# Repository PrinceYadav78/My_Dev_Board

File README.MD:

##Note i dont want funding of 16$ as this includes a part of a different project

# RP2040 Breadboard-Friendly Devboard

A compact RP2040 devboard designed for rapid prototyping and breadboard use. This board allows testing GPIOs, sensors, and ideas without soldering every change.

## What is this?
This project is a small PCB with an RP2040 microcontroller, USB-C power input, and breadboard-compatible headers. It is designed to allow quick circuit testing, firmware development, and learning without requiring a polished final product.

## Why I made it
I wanted a board that could power over USB and plug directly into a breadboard for rapid experimentation. By designing this board, I learned how to plan pinout, power, and I/O for a microcontroller, while also learning schematic design and PCB layout in KiCad.

## How it works
Power enters via USB-C and goes through basic regulation and decoupling capacitors for stability. The RP2040 handles I/O and communicates with peripherals like an IMU (ICM-20602). LEDs indicate power, BootSel, and GPIO activity. Breadboard headers allow plugging in sensors or modules quickly, and proper routing ensures signal integrity and safe operation.

### Key features
- USB-C powered RP2040 board  
- Breadboard-compatible header layout  
- LEDs for power, BootSel, and GPIO  
- Integrated IMU (ICM-20602) with required decoupling caps  
- Crystal oscillator for accurate timing  
- Boot configuration with button and pull-ups  

## What I learned
- Schematic clean ≠ correct: always check net names and pin mapping  
- QSPI pins on RP2040 must go to dedicated flash pins for booting  
- Routing power and USB signals is tricky; differential pairs and trace lengths matter  
- Component placement affects ease of routing and board functionality  
- Breadboard compatibility must be considered from the start  

##Images of pcb, sch, cost, bom, etc

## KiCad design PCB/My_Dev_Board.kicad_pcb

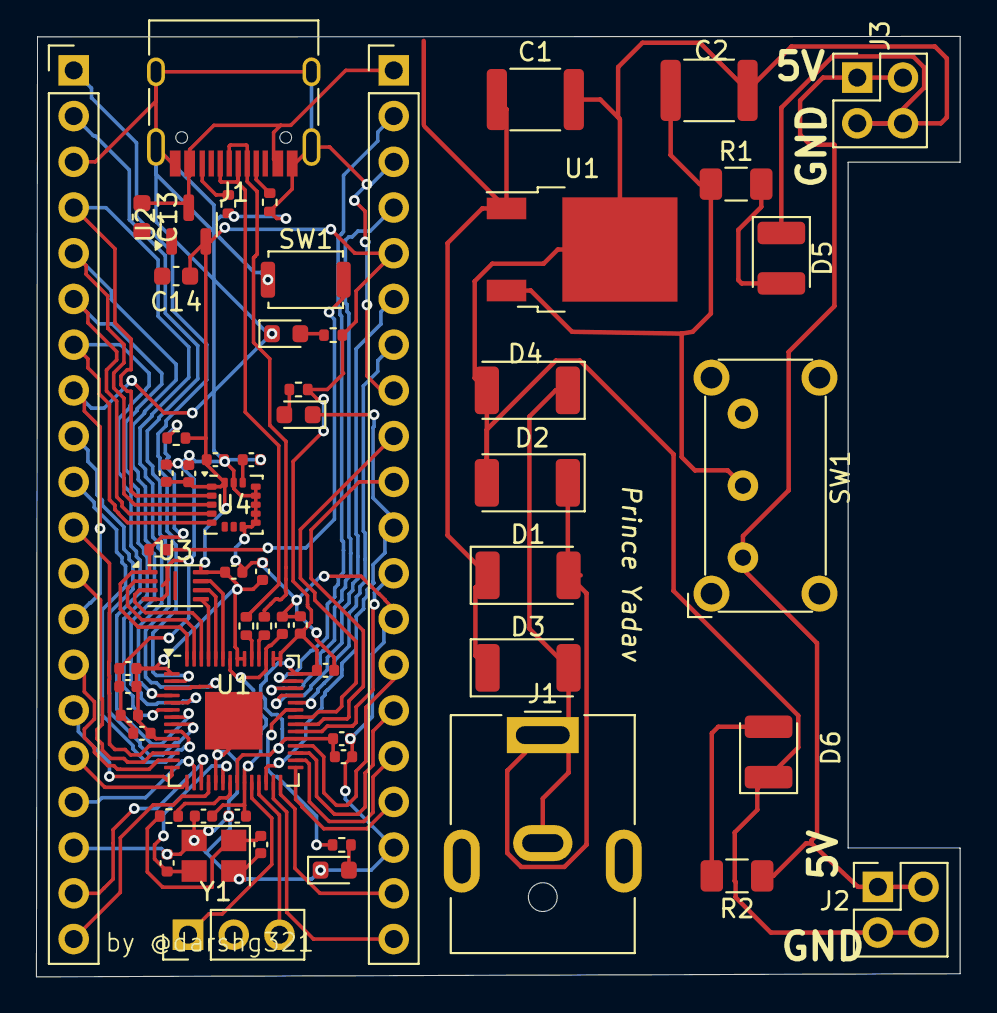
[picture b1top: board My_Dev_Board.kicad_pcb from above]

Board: 2 copper layers, 51.3 x 52.2 mm, 59 parts (0 on the bottom side), 65 nets.

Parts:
C1, C2#2, C3, C4, C5, C6, C7, C8, C10, C11, C17, C18, C20: 0.1uF; C_0402_1005Metric
C1#2: 47uF; C_1812_4532Metric
C2: 470uF; C_1812_4532Metric
C9, C12: 1uF; C_0402_1005Metric
C13, C14: 10uF; C_0603_1608Metric
C15, C16: 33pF; C_0402_1005Metric
C19: 10nF; C_0402_1005Metric
C21: 2.2uF; C_0402_1005Metric
D1, D2#2, D3: LED; LED_0603_1608Metric
D1#2, D2, D3#2, D4: 1N4007; D_2010_5025Metric
D5, D6: LED; LED_1210_3225Metric
J1: Barrel_Jack_Switch; BarrelJack_CUI_PJ-063AH_Horizontal
J1#2: USB_C_Receptacle_USB2.0_14P; USB_C_Receptacle_HRO_TYPE-C-31-M-12
J2, J3#2: Conn_01x20; PinHeader_1x20_P2.54mm_Vertical
J2#2, J3: Conn_02x02_Counter_Clockwise; PinHeader_2x02_P2.54mm_Vertical
J4: Conn_01x03; PinHeader_1x03_P2.54mm_Vertical
R1, R2#2: 560; R_1206_3216Metric
R1#2, R2: 5.1K; R_0402_1005Metric
R3, R4: 27; R_0402_1005Metric
R5, R7: 1K; R_0402_1005Metric
R6: 10K; R_0402_1005Metric
R8, R9, R10: 680; R_0402_1005Metric
SW1: SW_Push; SW_Push_SPST_NO_Alps_SKRK
SW1#2: SW_DPDT_x2; SW_E-Switch_EG1224_SPDT_Angled
U1: RP2040; QFN-56-1EP_7x7mm_P0.4mm_EP3.2x3.2mm
U1#2: LM7805_TO220; TO-252-2
U2: MCP1700x-330xxTT; SOT-23
U3: W25Q128JVS; Winbond_USON-8-1EP_3x2mm_P0.5mm_EP0.2x1.6mm
U4: ICM-20602; LGA-16_3x3mm_P0.5mm_LayoutBorder3x5y
Y1: 12MHz; Crystal_SMD_3225-4Pin_3.2x2.5mm

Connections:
+1V1: C10.1, C11.1, C12.1, U1.23 (DVDD), U1.45 (VREG_VOUT), U1.50 (DVDD)
+3V3: C1.1, C2#2.1, C3.1, C4.1, C5.1, C6.1, C7.1, C8.1, C9.1, C14.1, C17.1, C19.1, C20.2, C21.2, J3#2.5, R6.1, R8.1, R9.1, U1.1 (IOVDD), U1.10 (IOVDD), U1.22 (IOVDD), U1.33 (IOVDD), U1.42 (IOVDD), U1.43 (ADC_AVDD), U1.44 (VREG_IN), U1.48 (USB_VDD), U1.49 (IOVDD), U2.2 (VO), U3.8 (VCC), U4.1 (VDDIO), U4.16 (VDD)
/V-: C1#2.2, C2.2, D2.2, D4.2, D5.1, D6.1, J2#2.3, J2#2.4, J3.3, J3.4, U1#2.2
/Vin: C1#2.1, D1#2.1, D3#2.1, U1#2.1
/Vout1: C2.1, R1.1, SW1#2.2, U1#2.3
GND: C1.2, C2#2.2, C3.2, C4.2, C5.2, C6.2, C7.2, C8.2, C9.2, C10.2, C11.2, C12.2, C13.2, C14.2, C15.1, C16.1, C17.2, C18.2, C19.2, C20.1, C21.1, D1.1 (K), D3.1 (K), J1#2.A1 (GND), J1#2.A12 (GND), J1#2.B1 (GND), J1#2.B12 (GND), J1#2.S1 (SHIELD), J2.3, J2.8, J2.13, J2.18, J3#2.3, J3#2.8, J3#2.13, J3#2.18, J4.2, R1#2.2, R2.2, SW1.1, U1.19 (TESTEN), U1.57 (GND), U2.1 (GND), U3.4 (GND), U4.8 (FSYNC), U4.9 (GND), U4.10 (GND), U4.11 (GND), U4.12 (GND), U4.13 (GND), U4.15 (GND), Y1.2, Y1.4
GPIO0: J2.1, U1.2 (GPIO0)
GPIO1: J2.2, U1.3 (GPIO1)
GPIO2: J2.4, U1.4 (GPIO2), U4.2 (SCL/SPC)
GPIO3: J2.5, U1.5 (GPIO3), U4.3 (SDA/SDI)
GPIO4: J2.6, U1.6 (GPIO4), U4.4 (SAO/SD0)
GPIO5: J2.7, U1.7 (GPIO5), U4.5 (~CS)
GPIO6: J2.9, U1.8 (GPIO6)
GPIO7: J2.10, U1.9 (GPIO7)
GPIO8: J2.11, U1.11 (GPIO8)
GPIO9: J2.12, U1.12 (GPIO9)
GPIO10: J2.14, U1.13 (GPIO10)
GPIO11: J2.15, U1.14 (GPIO11)
GPIO12: J2.16, U1.15 (GPIO12)
GPIO13: J2.17, U1.16 (GPIO13)
GPIO14: J2.19, U1.17 (GPIO14)
GPIO15: J2.20, U1.18 (GPIO15)
GPIO16: J3#2.20, U1.27 (GPIO16)
GPIO17: J3#2.19, U1.28 (GPIO17)
GPIO18: J3#2.17, U1.29 (GPIO18)
GPIO19: J3#2.16, U1.30 (GPIO19)
GPIO20: J3#2.15, U1.31 (GPIO20)
GPIO21: J3#2.14, U1.32 (GPIO21)
GPIO22: J3#2.12, U1.34 (GPIO22)
GPIO23: J3#2.10, U1.35 (GPIO23)
GPIO24: J3#2.9, U1.36 (GPIO24)
GPIO25: R10.1, U1.37 (GPIO25)
GPIO26_ADC0: J3#2.7, U1.38 (GPIO26_ADC0)
GPIO27_ADC1: J3#2.6, U1.39 (GPIO27_ADC1)
GPIO28_ADC2: J3#2.4, U1.40 (GPIO28_ADC2)
GPIO29_ADC3: J3#2.2, U1.41 (GPIO29_ADC3)
unnamed: C16.2, R5.1, Y1.1
unnamed: D1.2 (A), R8.2
unnamed: D1#2.2, D2.1, J1.1
unnamed: D2#2.2 (A), R9.2
unnamed: D3.2 (A), R10.2
unnamed: D3#2.2, D4.1, J1.2
unnamed: D5.2, R1.2
unnamed: D6.2, R2#2.2
unnamed: J1#2.A5 (CC1), R1#2.1
unnamed: J1#2.B5 (CC2), R2.1
unnamed: J2#2.1, J2#2.2, J3.1, J3.2, R2#2.1, SW1#2.1
unnamed: R7.2, SW1.2
unnamed: R4.2, U1.46 (USB_DM)
unnamed: R3.2, U1.47 (USB_DP)
unnamed: C18.1, U4.14 (REGOUT)
QSPI_CLK: U1.52 (QSPI_SCLK), U3.6 (CLK)
QSPI_SD0: U1.53 (QSPI_SD0), U3.5 (DI/IO_{0})
QSPI_SD1: U1.55 (QSPI_SD1), U3.2 (DO/IO_{1})
QSPI_SD2: U1.54 (QSPI_SD2), U3.3 (~WP/IO_{2})
QSPI_SD3: U1.51 (QSPI_SD3), U3.7 (~HOLD/~RESET/IO_{3})
QSPI_SS: R6.2, R7.1, U1.56 (QSPI_SS), U3.1 (~CS)
RUN: D2#2.1 (K), J3#2.11, U1.26 (RUN)
SWCLK: J4.1, U1.24 (SWCLK)
SWD: J4.3, U1.25 (SWD)
USB_D+: J1#2.A6 (D+), J1#2.B6 (D+), R3.1
USB_D-: J1#2.A7 (D-), J1#2.B7 (D-), R4.1
VBUS: C13.1, J1#2.A4 (VBUS), J1#2.A9 (VBUS), J1#2.B4 (VBUS), J1#2.B9 (VBUS), J3#2.1, U2.3 (VI)
XIN: C15.2, U1.20 (XIN), Y1.3
XOUT: R5.2, U1.21 (XOUT)

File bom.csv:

Designator,Footprint,Quantity,Value,LCSC Part #
"C1_2, C10, C11, C17, C18, C2, C20, C3, C4, C5, C6, C7, C8",0402,13,0.1uF,
C1,1812,1,47uF,
"C12, C9",0402,2,1uF,
"C13, C14",0603,2,10uF,
"C15, C16",0402,2,33pF,
C19,0402,1,10nF,
C2_2,1812,1,470uF,
C21,0402,1,2.2uF,
"D1_2, D2, D3_2",0603,3,LED,
"D1, D2_2, D3, D4",2010,4,1N4007,
"D5, D6",1210,2,LED,
J1_2,BarrelJack_CUI_PJ-063AH_Horizontal,1,Barrel_Jack_Switch,
J1,USB_C_Receptacle_HRO_TYPE-C-31-M-12,1,USB_C_Receptacle_USB2.0_14P,
"J2_2, J3",PinHeader_1x20_P2.54mm_Vertical,2,Conn_01x20,
"J2, J3_2",PinHeader_2x02_P2.54mm_Vertical,2,Conn_02x02_Counter_Clockwise,
J4,PinHeader_1x03_P2.54mm_Vertical,1,Conn_01x03,
"R1_2, R2",1206,2,560,
"R1, R2_2",0402,2,5.1K,
"R10, R8, R9",0402,3,680,
"R3, R4",0402,2,27,
"R5, R7",0402,2,1K,
R6,0402,1,10K,
SW1_2,SW_Push_SPST_NO_Alps_SKRK,1,SW_Push,
SW1,SW_E-Switch_EG1224_SPDT_Angled,1,SW_DPDT_x2,
U1_2,QFN-56-1EP_7x7mm_P0.4mm_EP3.2x3.2mm,1,RP2040,
U1,TO-252-2,1,LM7805_TO220,
U2,SOT-23,1,MCP1700x-330xxTT,
U3,Winbond_USON-8-1EP_3x2mm_P0.5mm_EP0.2x1.6mm,1,W25Q128JVS,
U4,LGA-16_3x3mm_P0.5mm_LayoutBorder3x5y,1,ICM-20602,
Y1,Crystal_SMD_3225-4Pin_3.2x2.5mm,1,12MHz,
